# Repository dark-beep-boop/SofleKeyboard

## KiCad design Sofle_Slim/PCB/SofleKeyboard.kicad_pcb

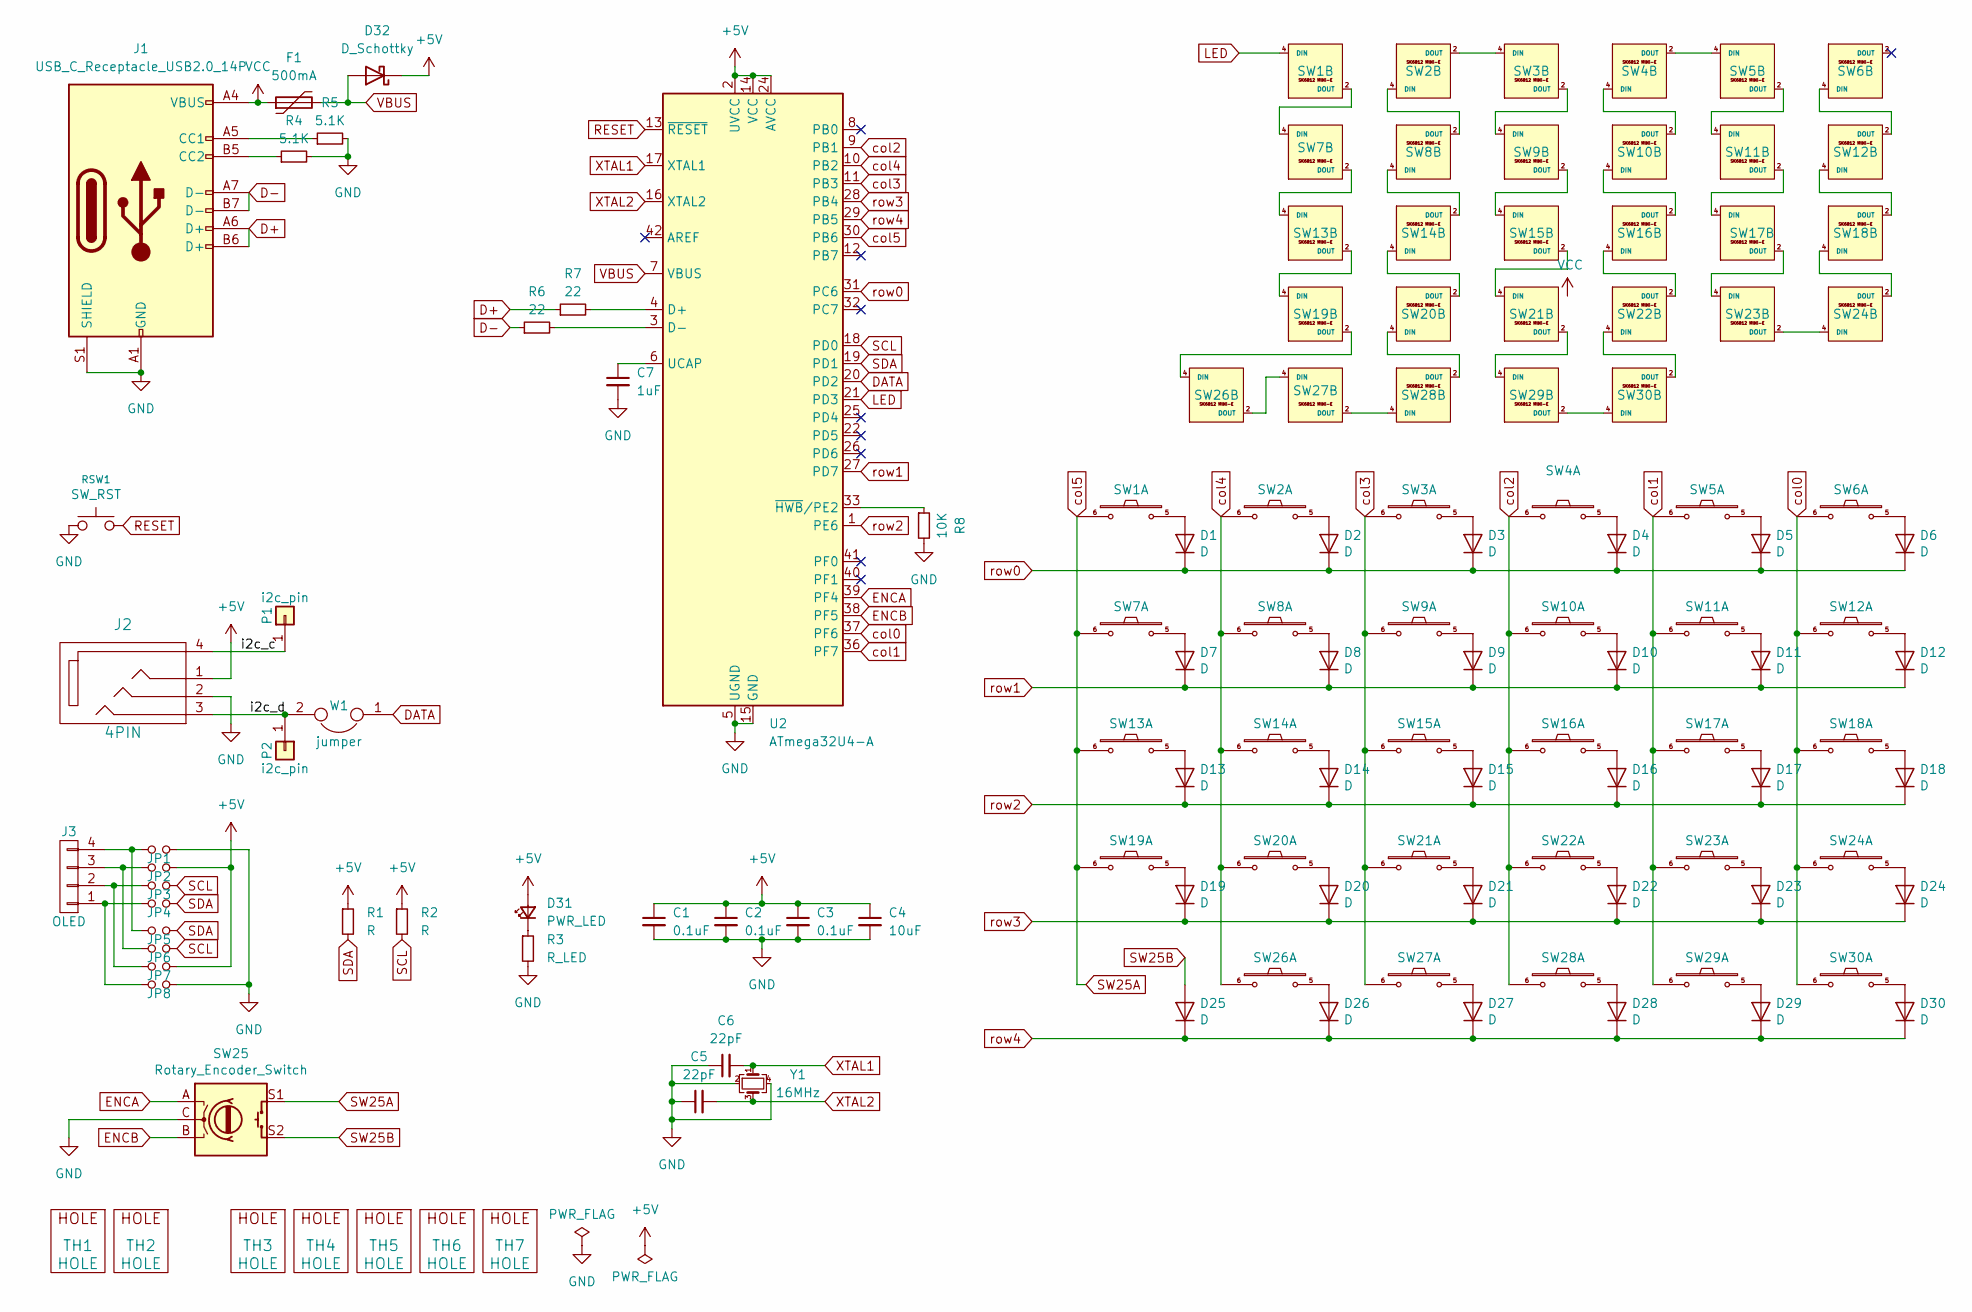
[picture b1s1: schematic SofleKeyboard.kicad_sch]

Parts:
C1, C2, C3: 0.1uF; C_0805_2012Metric
C4: 10uF; C_0805_2012Metric
C5, C6: 22pF; C_0805_2012Metric
C7: 1uF; C_0805_2012Metric
D1, D2, D3, D4, D5, D6, D7, D8, D9, D10, D11, D12, D13, D14, D15, D16, D17, D18, D19, D20, D21, D22, D23, D24, D25, D26, D27, D28, D29, D30: D; crkbd-diode
D31: PWR_LED; LED_0805_2012Metric
D32: D_Schottky; D_SOD-123F
F1: 500mA; Fuse_1206_3216Metric
J1: USB_C_Receptacle_USB2.0_14P; USB_C_Receptacle_Molex_105450-0101
J2: 4PIN; MJ-4PP-9
J3: OLED; OLED_4Pin
JP1, JP2, JP3, JP4, JP5, JP6, JP7, JP8: Jumper_NO_Small; Jumper
P1, P2: i2c_pin; 1pin_conn
R1, R2: R; R_0805_2012Metric
R3: R_LED; R_0805_2012Metric
R4, R5: 5.1K; R_0805_2012Metric
R6, R7: 22; R_0805_2012Metric
R8: 10K; R_0805_2012Metric
RSW1: SW_RST; TACT_SWITCH_TVBP06
SW1, SW2, SW3, SW4, SW5, SW6, SW7, SW8, SW9, SW10, SW11, SW12, SW13, SW14, SW15, SW16, SW17, SW18, SW19, SW20, SW21, SW22, SW23, SW24, SW26, SW27, SW28, SW29, SW30: SW_PUSH_LED; Choc_Hotswap_SK6812MiniE
SW25: Rotary_Encoder_Switch; RotaryEncoder_Alps_EC11E-Switch_Vertical_H20mm-keebio_modif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
TH1, TH2: HOLE; M2_HOLE_PCB
TH3, TH4, TH5, TH6, TH7: HOLE; HOLE_M2_TH
U2: ATmega32U4-A; TQFP-44_10x10mm_P0.8mm
W1: jumper; jumper_data
Y1: 16MHz; Crystal_SMD_3225-4Pin_3.2x2.5mm

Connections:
+5V: C1.1, C2.1, C3.1, C4.1, D31.2 (A), D32.1 (K), J2.1, JP2.2, JP7.2, R1.1, R2.1, U2.2 (UVCC), U2.14 (VCC), U2.24 (AVCC), U2.34 (VCC), U2.44 (AVCC)
/i2c_c: J2.4, P1.1
/i2c_d: J2.3, P2.1, W1.2
D+: J1.A6 (D+), J1.B6 (D+), R7.1
D-: J1.A7 (D-), J1.B7 (D-), R6.1
DATA: U2.20 (PD2), W1.1
ENCA: SW25.A, U2.39 (PF4)
ENCB: SW25.B, U2.38 (PF5)
GND: C1.2, C2.2, C3.2, C4.2, C5.1, C6.1, C7.2, J1.A1 (GND), J1.A12 (GND), J1.B1 (GND), J1.B12 (GND), J1.S1 (SHIELD), J2.2, JP1.2, JP8.2, R3.2, R4.2, R5.2, R8.2, RSW1.1, SW1.3 (GND), SW2.3 (GND), SW3.3 (GND), SW4.3 (GND), SW5.3 (GND), SW6.3 (GND), SW7.3 (GND), SW8.3 (GND), SW9.3 (GND), SW10.3 (GND), SW11.3 (GND), SW12.3 (GND), SW13.3 (GND), SW14.3 (GND), SW15.3 (GND), SW16.3 (GND), SW17.3 (GND), SW18.3 (GND), SW19.3 (GND), SW20.3 (GND), SW21.3 (GND), SW22.3 (GND), SW23.3 (GND), SW24.3 (GND), SW25.C, SW26.3 (GND), SW27.3 (GND), SW28.3 (GND), SW29.3 (GND), SW30.3 (GND), U2.5 (UGND), U2.15 (GND), U2.23 (GND), U2.35 (GND), U2.43 (GND), Y1.2, Y1.4
LED: SW1.4 (DIN), U2.21 (PD3)
unnamed: D1.2 (A), SW1.5
unnamed: D2.2 (A), SW2.5
unnamed: D3.2 (A), SW3.5
unnamed: D4.2 (A), SW4.5
unnamed: D5.2 (A), SW5.5
unnamed: D6.2 (A), SW6.5
unnamed: D7.2 (A), SW7.5
unnamed: D8.2 (A), SW8.5
unnamed: D9.2 (A), SW9.5
unnamed: D10.2 (A), SW10.5
unnamed: D11.2 (A), SW11.5
unnamed: D12.2 (A), SW12.5
unnamed: D13.2 (A), SW13.5
unnamed: D14.2 (A), SW14.5
unnamed: D15.2 (A), SW15.5
unnamed: D16.2 (A), SW16.5
unnamed: D17.2 (A), SW17.5
unnamed: D18.2 (A), SW18.5
unnamed: D19.2 (A), SW19.5
unnamed: D20.2 (A), SW20.5
unnamed: D21.2 (A), SW21.5
unnamed: D22.2 (A), SW22.5
unnamed: D23.2 (A), SW23.5
unnamed: D24.2 (A), SW24.5
unnamed: D26.2 (A), SW26.5
unnamed: D27.2 (A), SW27.5
unnamed: D28.2 (A), SW28.5
unnamed: D29.2 (A), SW29.5
unnamed: D30.2 (A), SW30.5
unnamed: D31.1 (K), R3.1
unnamed: J1.A5 (CC1), R5.1
unnamed: J1.B5 (CC2), R4.1
unnamed: J3.1, JP4.1, JP8.1
unnamed: J3.2, JP3.1, JP7.1
unnamed: J3.3, JP2.1, JP6.1
unnamed: J3.4, JP1.1, JP5.1
unnamed: SW1.2 (DOUT), SW7.4 (DIN)
unnamed: SW2.4 (DIN), SW8.2 (DOUT)
unnamed: SW2.2 (DOUT), SW3.4 (DIN)
unnamed: SW3.2 (DOUT), SW9.4 (DIN)
unnamed: SW4.2 (DOUT), SW5.4 (DIN)
unnamed: SW10.4 (DIN), SW16.2 (DOUT)
unnamed: SW4.4 (DIN), SW10.2 (DOUT)
unnamed: SW5.2 (DOUT), SW11.4 (DIN)
unnamed: SW11.2 (DOUT), SW17.4 (DIN)
unnamed: SW12.4 (DIN), SW18.2 (DOUT)
unnamed: SW6.4 (DIN), SW12.2 (DOUT)
unnamed: SW7.2 (DOUT), SW13.4 (DIN)
unnamed: SW13.2 (DOUT), SW19.4 (DIN)
unnamed: SW14.4 (DIN), SW20.2 (DOUT)
unnamed: SW8.4 (DIN), SW14.2 (DOUT)
unnamed: SW9.2 (DOUT), SW15.4 (DIN)
unnamed: SW15.2 (DOUT), SW21.4 (DIN)
unnamed: SW16.4 (DIN), SW22.2 (DOUT)
unnamed: SW17.2 (DOUT), SW23.4 (DIN)
unnamed: SW18.4 (DIN), SW24.2 (DOUT)
unnamed: SW19.2 (DOUT), SW26.4 (DIN)
unnamed: SW20.4 (DIN), SW28.2 (DOUT)
unnamed: SW21.2 (DOUT), SW29.4 (DIN)
unnamed: SW22.4 (DIN), SW30.2 (DOUT)
unnamed: SW23.2 (DOUT), SW24.4 (DIN)
unnamed: SW26.2 (DOUT), SW27.4 (DIN)
unnamed: SW27.2 (DOUT), SW28.4 (DIN)
unnamed: SW29.2 (DOUT), SW30.4 (DIN)
unnamed: R7.2, U2.4 (D+)
unnamed: R6.2, U2.3 (D-)
unnamed: C7.1, U2.6 (UCAP)
unnamed: R8.1, U2.33 (~HWB/PE2)
RESET: RSW1.2, U2.13 (~RESET)
SCL: JP3.2, JP6.2, R2.2, U2.18 (PD0)
SDA: JP4.2, JP5.2, R1.2, U2.19 (PD1)
SW25A: SW1.6, SW7.6, SW13.6, SW19.6, SW25.S1, U2.30 (PB6)
SW25B: D25.2 (A), SW25.S2
VBUS: D32.2 (A), F1.2, U2.7 (VBUS)
VCC: F1.1, J1.A4 (VBUS), J1.A9 (VBUS), J1.B4 (VBUS), J1.B9 (VBUS), SW1.1 (VDD), SW2.1 (VDD), SW3.1 (VDD), SW4.1 (VDD), SW5.1 (VDD), SW6.1 (VDD), SW7.1 (VDD), SW8.1 (VDD), SW9.1 (VDD), SW10.1 (VDD), SW11.1 (VDD), SW12.1 (VDD), SW13.1 (VDD), SW14.1 (VDD), SW15.1 (VDD), SW16.1 (VDD), SW17.1 (VDD), SW18.1 (VDD), SW19.1 (VDD), SW20.1 (VDD), SW21.1 (VDD), SW22.1 (VDD), SW23.1 (VDD), SW24.1 (VDD), SW26.1 (VDD), SW27.1 (VDD), SW28.1 (VDD), SW29.1 (VDD), SW30.1 (VDD)
XTAL1: C6.2, U2.17 (XTAL1), Y1.1
XTAL2: C5.2, U2.16 (XTAL2), Y1.3
col0: SW6.6, SW12.6, SW18.6, SW24.6, SW30.6, U2.37 (PF6)
col1: SW5.6, SW11.6, SW17.6, SW23.6, SW29.6, U2.36 (PF7)
col2: SW4.6, SW10.6, SW16.6, SW22.6, SW28.6, U2.9 (PB1)
col3: SW3.6, SW9.6, SW15.6, SW21.6, SW27.6, U2.11 (PB3)
col4: SW2.6, SW8.6, SW14.6, SW20.6, SW26.6, U2.10 (PB2)
row0: D1.1 (K), D2.1 (K), D3.1 (K), D4.1 (K), D5.1 (K), D6.1 (K), U2.31 (PC6)
row1: D7.1 (K), D8.1 (K), D9.1 (K), D10.1 (K), D11.1 (K), D12.1 (K), U2.27 (PD7)
row2: D13.1 (K), D14.1 (K), D15.1 (K), D16.1 (K), D17.1 (K), D18.1 (K), U2.1 (PE6)
row3: D19.1 (K), D20.1 (K), D21.1 (K), D22.1 (K), D23.1 (K), D24.1 (K), U2.28 (PB4)
row4: D25.1 (K), D26.1 (K), D27.1 (K), D28.1 (K), D29.1 (K), D30.1 (K), U2.29 (PB5)

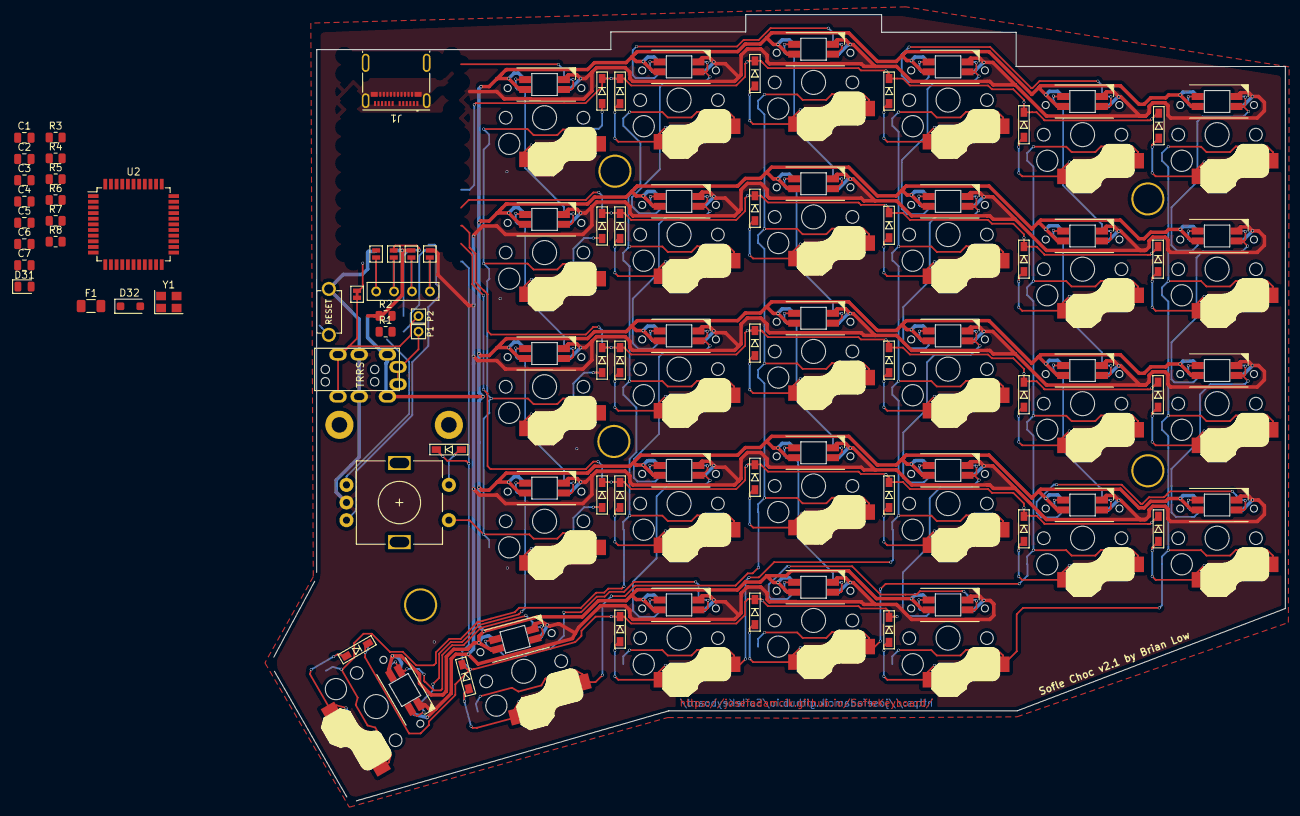
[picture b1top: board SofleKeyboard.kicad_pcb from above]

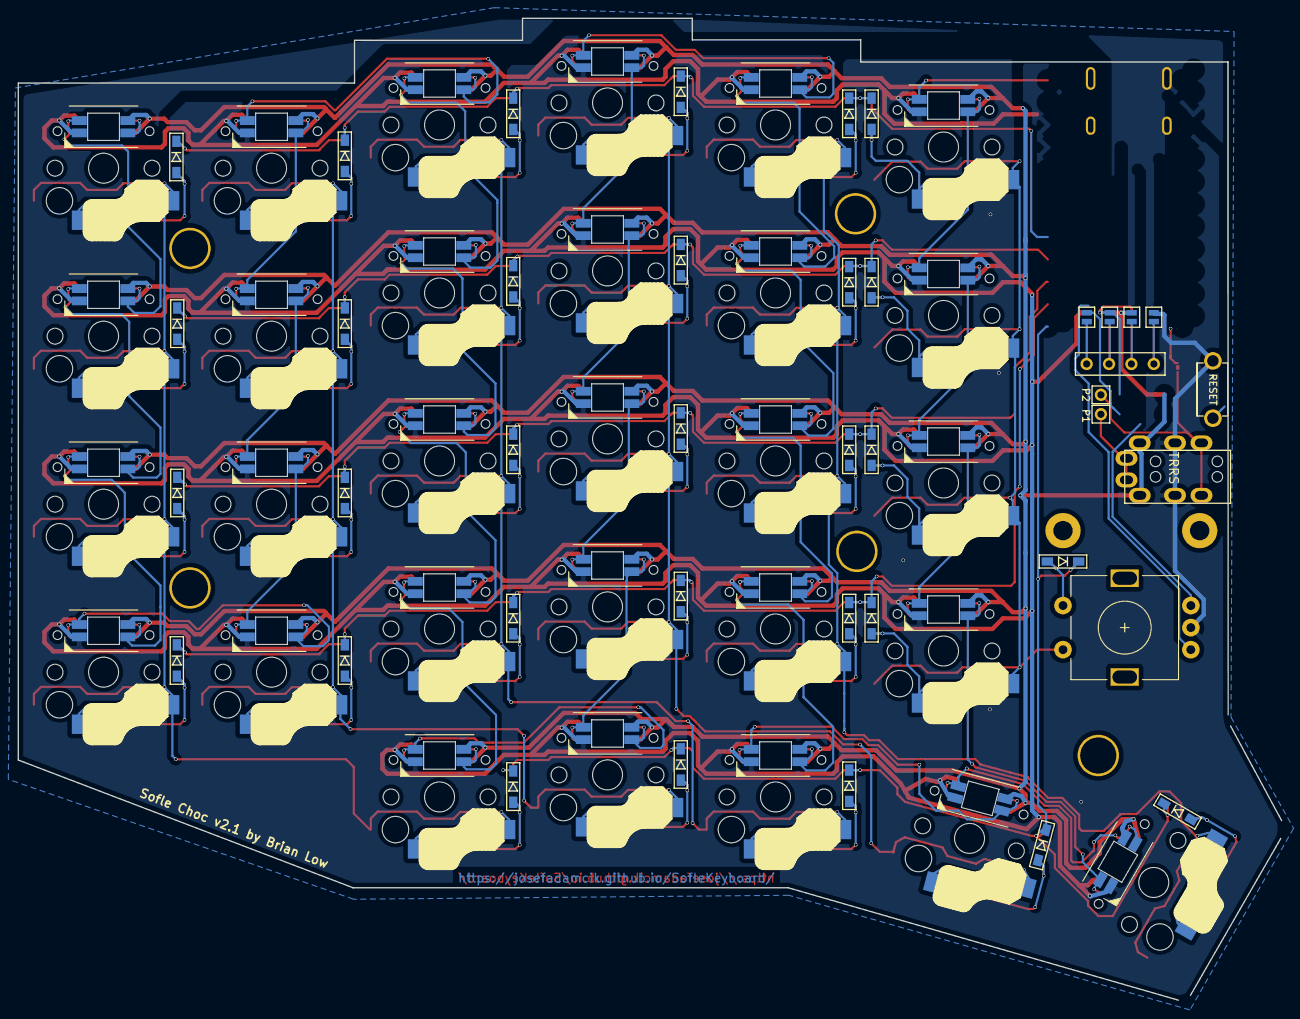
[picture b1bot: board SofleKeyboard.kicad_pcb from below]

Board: 2 copper layers, 143.3 x 111.3 mm, 102 parts (4 on the bottom side), 97 nets.

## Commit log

2024-02-08 slim design separated
2024-02-08 scheme modified
2024-02-10 changed usb-c plug for usb receptacle
2024-02-11 PCB work in progress
